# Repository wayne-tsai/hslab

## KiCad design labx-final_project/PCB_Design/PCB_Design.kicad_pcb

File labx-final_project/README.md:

# PAGER (BEEPER)

## Overview
The PAGER (BEEPER) is a wireless telecommunications system based on Meshtastic LoRa mesh technology. It consists of individual beeper devices that can communicate with each other and a central dashboard display for monitoring and management. The system is designed for precise location tracking and efficient communication in remote or off-grid areas.

---

## Beeper Devices (Sensor Device)

### Description
The beeper devices form a mesh network, allowing them to communicate with each other and share location data. Each beeper includes:

- **Main Board ([WiFi LoRa 32 V3.2](datasheets/HTIT-WB32LA_V3.2.pdf))**
- **GPS Module** ([NEO-6M GPS ](datasheets/NEO-6.pdf)): Provides accurate location tracking
- **LED Indicator**: Shows connection and battery status
- **Small Display (Onboard OLED)**: Shows essential status information
- **Battery**: Long-lasting rechargeable power source

Each beeper can:
- Track and broadcast its location
- Receive locations from other beepers in range
- Send and receive emergency signals
- Display basic status information
- Operate in the mesh network independently

### Sketch

---

## Central Dashboard Display (Display Device)

### Description
The central dashboard display acts as a management hub for the entire beeper network. It provides comprehensive monitoring and control capabilities:

- **Gauge**: Show direction of the specified device.
- **LED**: Show system status.
- **Button**: Allows navigation through the menu.
- **OLED Display ([SSD1306](datasheets/SSD1306.pdf))**: Shows locations and status of all beepers in the network

Key Features:
- Real-time tracking of all beepers
- Network health monitoring
- Configuration management

### Sketch

---

## Communication and Workflow

### Communication Overview
The system utilizes Meshtastic LoRa mesh technology for robust, long-range wireless communication. Beepers can communicate directly with each other and relay information through the mesh network to reach the central dashboard.

### Workflow Diagram
The system workflow includes:

1. Beeper devices continuously track their location via GPS
2. Each beeper broadcasts its location and status to the mesh network
3. Beepers relay messages from other devices to extend network range
4. The central dashboard:
   - Collects data from all beepers
   - Displays real-time network status
   - Manages device configurations
   - Monitors for alerts or emergencies

---

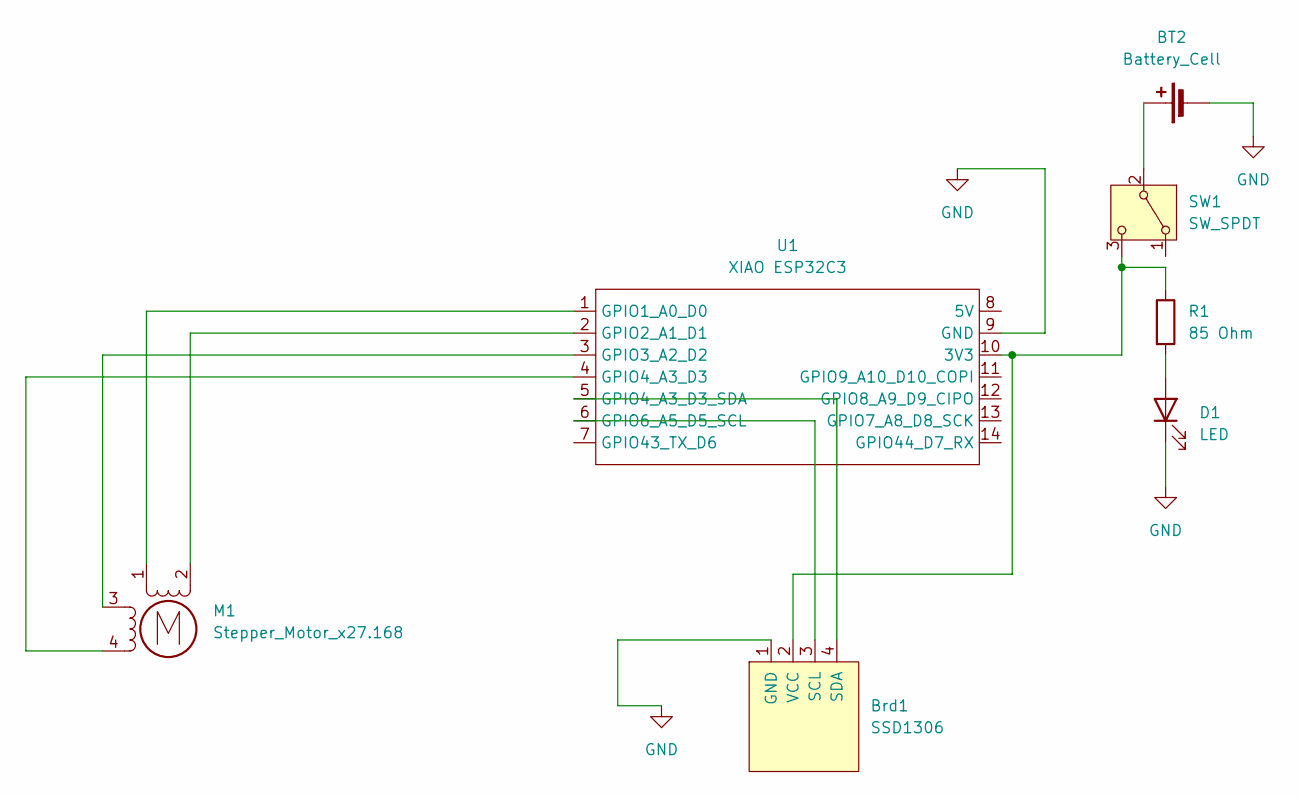
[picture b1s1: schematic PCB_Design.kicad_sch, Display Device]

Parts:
BT2: Battery_Cell; JST_PH_B2B-PH-K_1x02_P2.00mm_Vertical
Brd1: SSD1306; 128x64OLED
D1: LED; LED_D5.0mm
M1: Stepper_Motor_x27.168; x27_stepper
R1: 85 Ohm; R_Axial_DIN0207_L6.3mm_D2.5mm_P10.16mm_Horizontal
SW1: SW_SPDT; JST_EH_B3B-EH-A_1x03_P2.50mm_Vertical
U1: XIAO ESP32C3; XIAO_ESP32_SENSE

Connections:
GND: BT2.2 (-), Brd1.1 (GND), D1.1 (K), U1.9 (GND)
unnamed: BT2.1 (+), SW1.2 (B)
unnamed: Brd1.3 (SCL), U1.6 (GPIO6_A5_D5_SCL)
unnamed: Brd1.4 (SDA), U1.5 (GPIO4_A3_D3_SDA)
unnamed: Brd1.2 (VCC), R1.1, SW1.3 (C), U1.10 (3V3)
unnamed: D1.2 (A), R1.2
unnamed: M1.2 (-), U1.2 (GPIO2_A1_D1)
unnamed: M1.1, U1.1 (GPIO1_A0_D0)
unnamed: M1.3, U1.3 (GPIO3_A2_D2)
unnamed: M1.4, U1.4 (GPIO4_A3_D3)

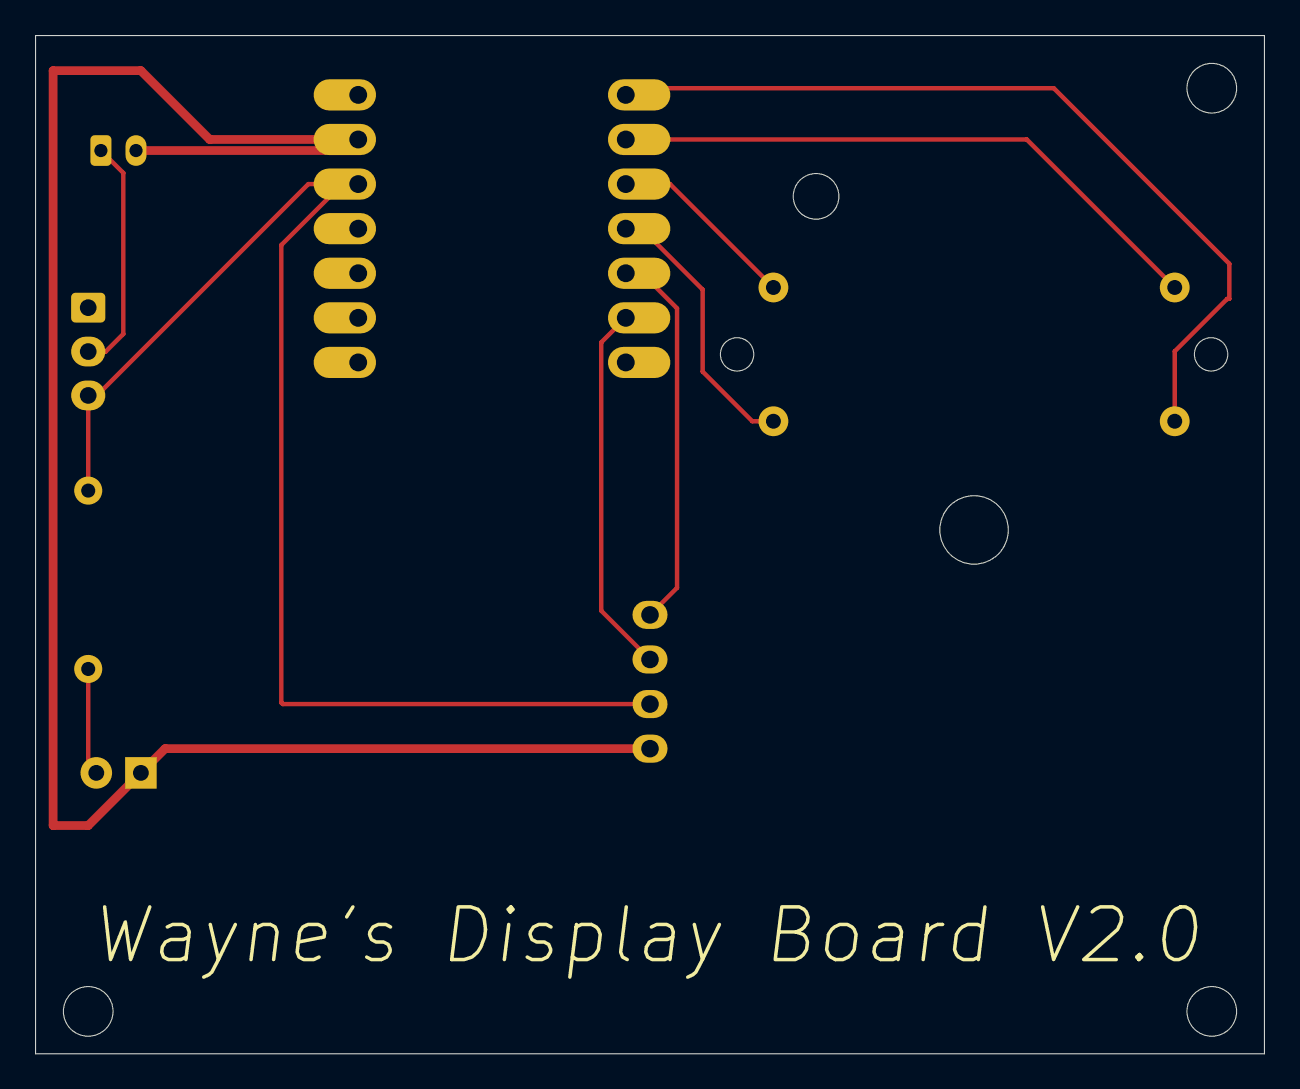
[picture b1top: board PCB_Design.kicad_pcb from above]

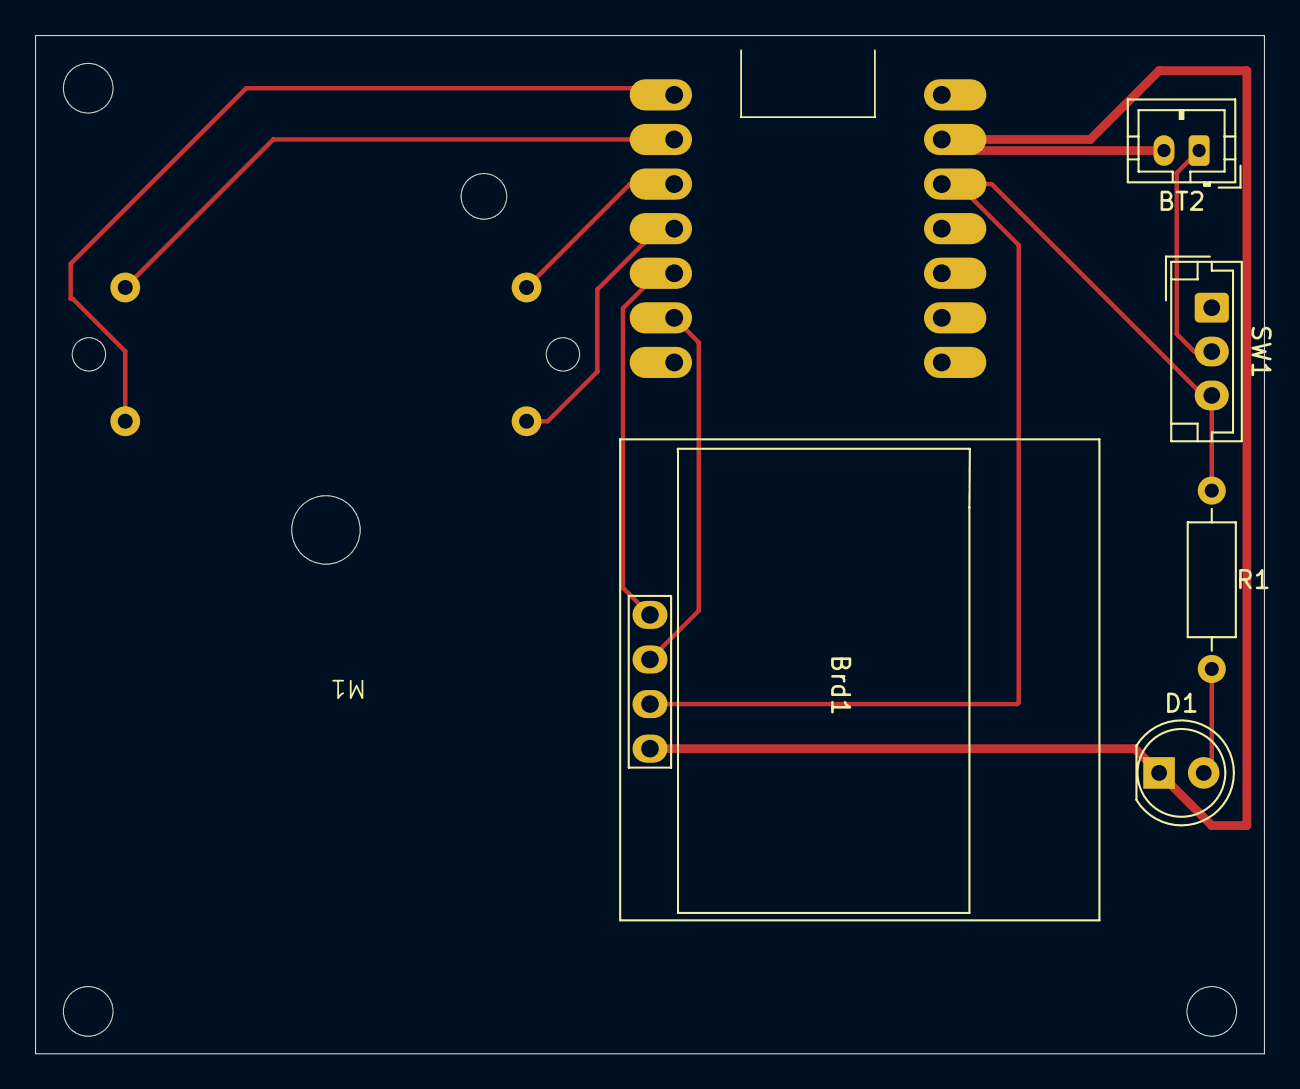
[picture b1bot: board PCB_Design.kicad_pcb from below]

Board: 2 copper layers, 70.0 x 58.0 mm, 7 parts (7 on the bottom side), 10 nets.

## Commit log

2025-02-06 finish lab5
2025-02-06 add github repo link for lab5
2025-02-06 add previous lab works
2025-02-08 first pcb run
2025-02-14 add battery_life_estimaiton
2025-02-28 add Second PCB Run
